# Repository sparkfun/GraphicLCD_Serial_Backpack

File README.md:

Graphic LCD Serial Backpack
============================
[
*Graphic LCD Serial Backpack(LCD-09352)*](https://www.sparkfun.com/products/9352)

The Graphic LCD Serial Backpack interfaces to either the [160x128 pixel Huge Graphic LCD](https://www.sparkfun.com/products/8799) or
the [128x64 pixel display](https://www.sparkfun.com/products/710). The backpack will allow you to write text, draw lines, circles and boxes, 
set and reset individual pixels, and erase specific blocks of the display. 

Repository Contents
-------------------
* **/Firmware** - The firmware that comes installed on the backpack
* **/Hardware** - All Eagle design files (.brd, .sch)

Product Versions
----------------
* [LCD-09352](https://www.sparkfun.com/products/9352)- Graphic Serial LCD Backpack by itself
* [LCD-09351](https://www.sparkfun.com/products/9351) - Serial Graphic LCD 128x64 (LCD + backpack)
* [LCD-08884](https://www.sparkfun.com/products/8884) - Serial Graphic LCD 160x128 (LCD + backpack)

License Information
-------------------
The hardware is released under [Creative Commons Share-alike 3.0](http://creativecommons.org/licenses/by-sa/3.0/).  
All other code is open source so please feel free to do anything you want with it; you buy me a beer if you use this and we meet someday ([Beerware license](http://en.wikipedia.org/wiki/Beerware)).

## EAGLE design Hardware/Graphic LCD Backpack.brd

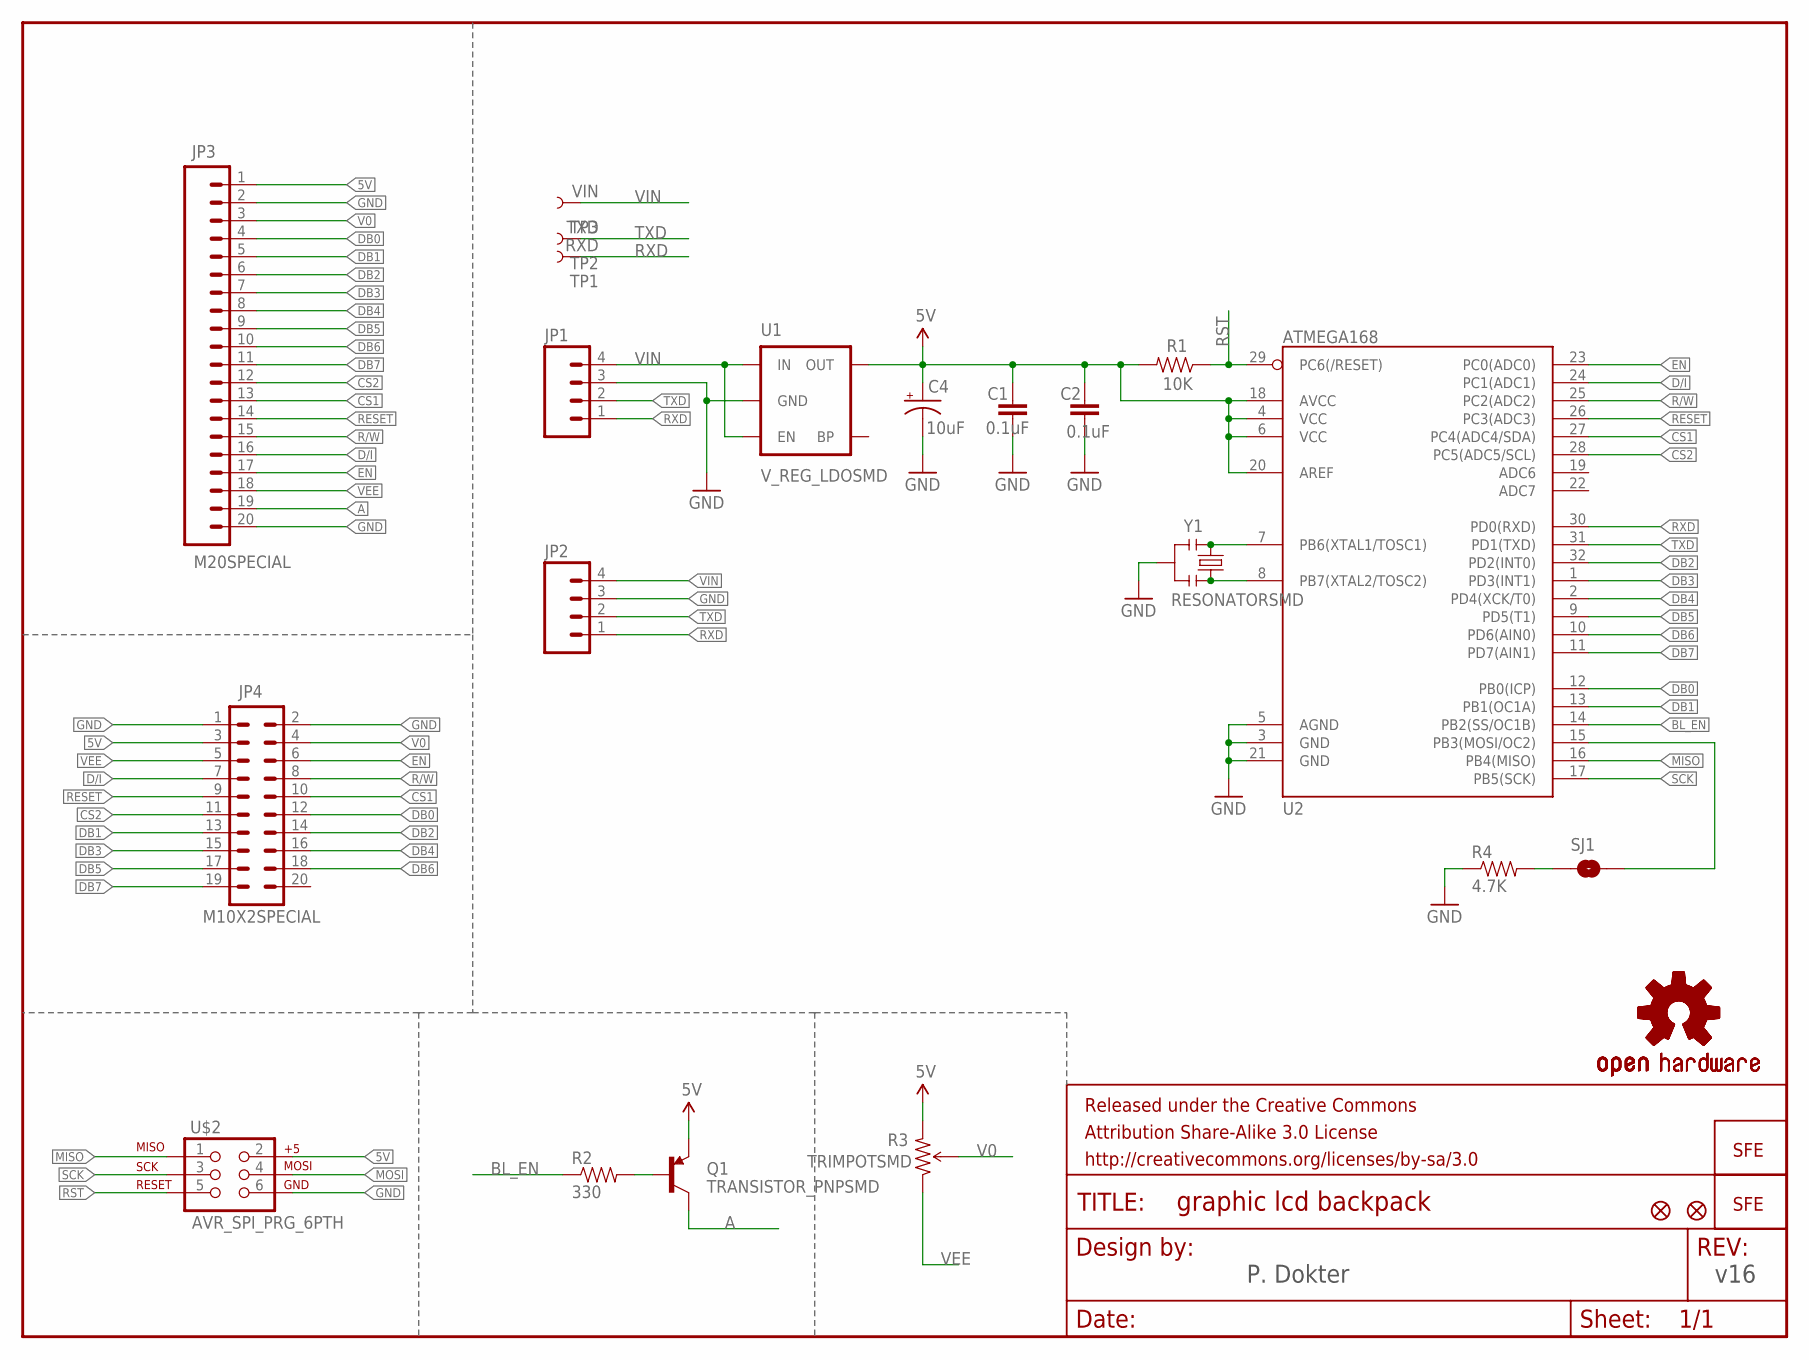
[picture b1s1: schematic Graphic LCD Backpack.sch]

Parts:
C1, C2: 0.1uF; 0603-CAP
C4: 10uF; EIA3216
FRAME1: FRAME-LETTER; CREATIVE_COMMONS
JP1: M04SMD; 1X04-SMD
JP2: M04PTH; 1X04
JP3: M20SPECIAL; 1X20_LOCK_SPECIAL
JP4: M10X2SPECIAL; 2X10_LOCK_SPECIAL
LOGO1: OSHW-LOGOL; OSHW-LOGO-L
LOGO2: LOGO-SFENEW; SFE-NEW-WEBLOGO
LOGO3: OSHW-LOGOS; OSHW-LOGO-S
Q1: TRANSISTOR_PNPSMD; SOT23-3
R1: 10K; 0603-RES
R2: 330; 0603-RES
R3: TRIMPOTSMD; TRIMPOT-3MM
R4: 4.7K; 0603-RES
SJ1: SOLDERJUMPERNC2; SJ_2S-NOTRACE
TP1: RXD; PAD.03X.05
TP2: TXD; PAD.03X.05
TP3: VIN; PAD.03X.05
U1: V_REG_LDOSMD; SOT23-5
U2: ATMEGA168; TQFP32-08
U$2: AVR_SPI_PRG_6PTH; 2X3
U$8: LOGO-SFENEW; SFE-NEW-WEBLOGO
U$9, U$10: FIDUCIAL1X2; FIDUCIAL-1X2
Y1: RESONATORSMD; RESONATOR-SMD

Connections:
5V: C1.1, C2.2, C4.A (+), JP3.1, JP4.3, Q1.2 (E), R1.2, R3.3 (CW), U1.5 (OUT), U2.4 (VCC), U2.6 (VCC), U2.18 (AVCC), U2.20 (AREF), U$2.2
A: JP3.19, Q1.3 (C)
BL_EN: R2.1, U2.14 (PB2(SS/OC1B))
CS1: JP3.13, JP4.10, U2.27 (PC4(ADC4/SDA))
CS2: JP3.12, JP4.11, U2.28 (PC5(ADC5/SCL))
D/I: JP3.16, JP4.7, U2.24 (PC1(ADC1))
DB0: JP3.4, JP4.12, U2.12 (PB0(ICP))
DB1: JP3.5, JP4.13, U2.13 (PB1(OC1A))
DB2: JP3.6, JP4.14, U2.32 (PD2(INT0))
DB3: JP3.7, JP4.15, U2.1 (PD3(INT1))
DB4: JP3.8, JP4.16, U2.2 (PD4(XCK/T0))
DB5: JP3.9, JP4.17, U2.9 (PD5(T1))
DB6: JP3.10, JP4.18, U2.10 (PD6(AIN0))
DB7: JP3.11, JP4.19, U2.11 (PD7(AIN1))
EN: JP3.17, JP4.6, U2.23 (PC0(ADC0))
GND: C1.2, C2.1, C4.C (-), JP1.3, JP2.3, JP3.2, JP3.20, JP4.1, JP4.2, R4.1, U1.2 (GND), U2.3 (GND), U2.5 (AGND), U2.21 (GND), U$2.6, Y1.2
MISO: U2.16 (PB4(MISO)), U$2.1
MOSI: SJ1.2, U2.15 (PB3(MOSI/OC2)), U$2.4
unnamed: Q1.1 (B), R2.2
unnamed: U2.7 (PB6(XTAL1/TOSC1)), Y1.1
unnamed: U2.8 (PB7(XTAL2/TOSC2)), Y1.3
unnamed: R4.2, SJ1.1
R/W: JP3.15, JP4.8, U2.25 (PC2(ADC2))
RESET: JP3.14, JP4.9, U2.26 (PC3(ADC3))
RST: R1.1, U2.29 (PC6(/RESET)), U$2.5
RXD: JP1.1, JP2.1, TP1.P$1, U2.30 (PD0(RXD))
SCK: U2.17 (PB5(SCK)), U$2.3
TXD: JP1.2, JP2.2, TP2.P$1, U2.31 (PD1(TXD))
V0: JP3.3, JP4.4, R3.2 (WIPER)
VEE: JP3.18, JP4.5, R3.1 (CCW)
VIN: JP1.4, JP2.4, TP3.P$1, U1.1 (IN), U1.3 (EN)

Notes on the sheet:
v16
P. Dokter

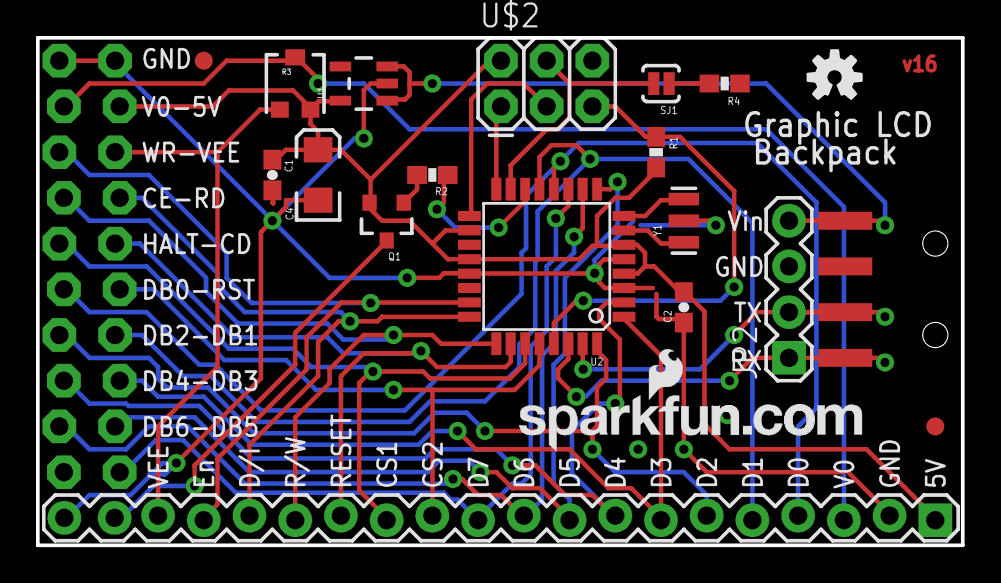
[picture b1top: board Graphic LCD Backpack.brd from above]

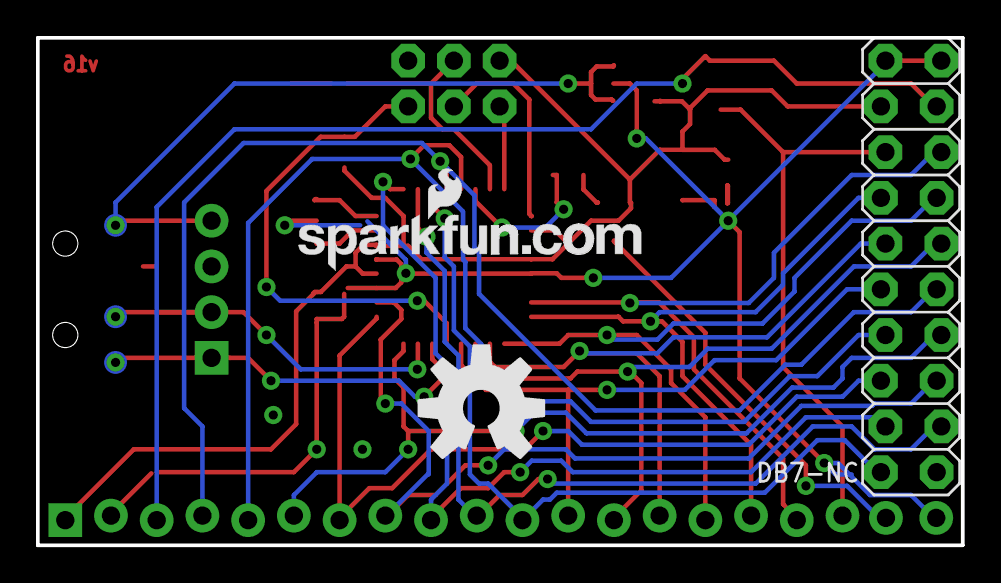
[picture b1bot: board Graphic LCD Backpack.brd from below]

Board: 2 copper layers, 51.4 x 28.2 mm, 27 parts (6 on the bottom side), 31 nets.

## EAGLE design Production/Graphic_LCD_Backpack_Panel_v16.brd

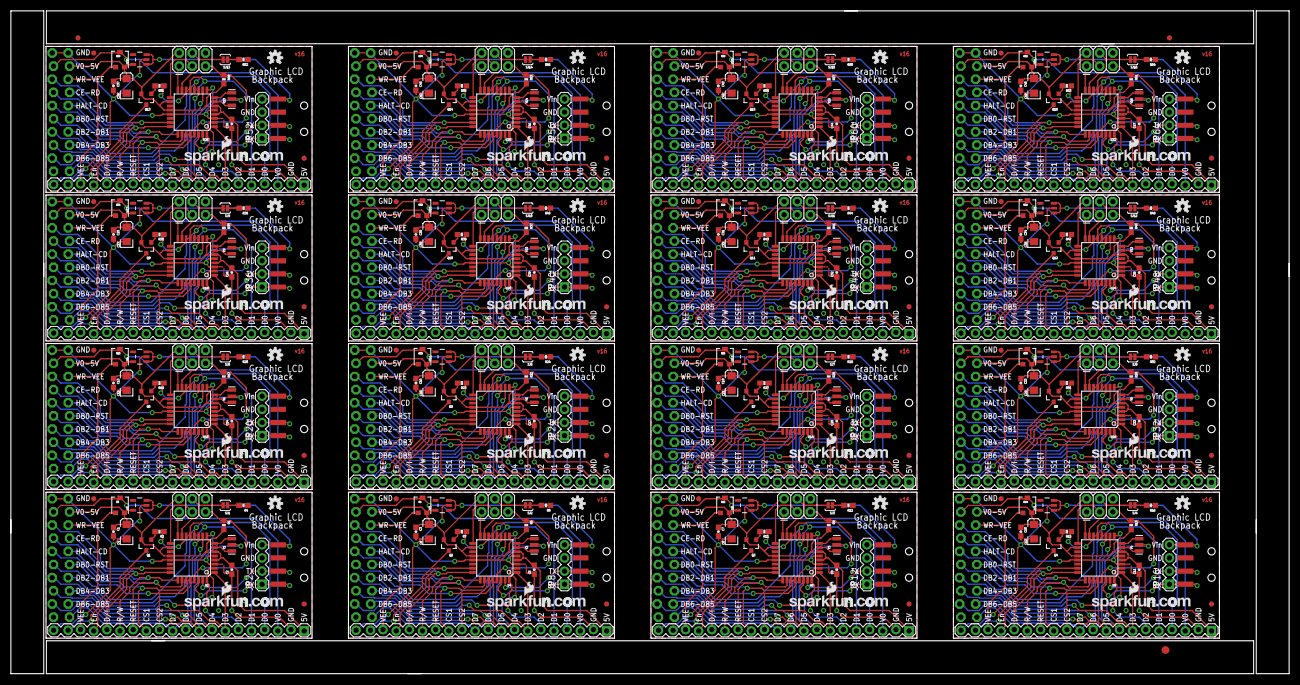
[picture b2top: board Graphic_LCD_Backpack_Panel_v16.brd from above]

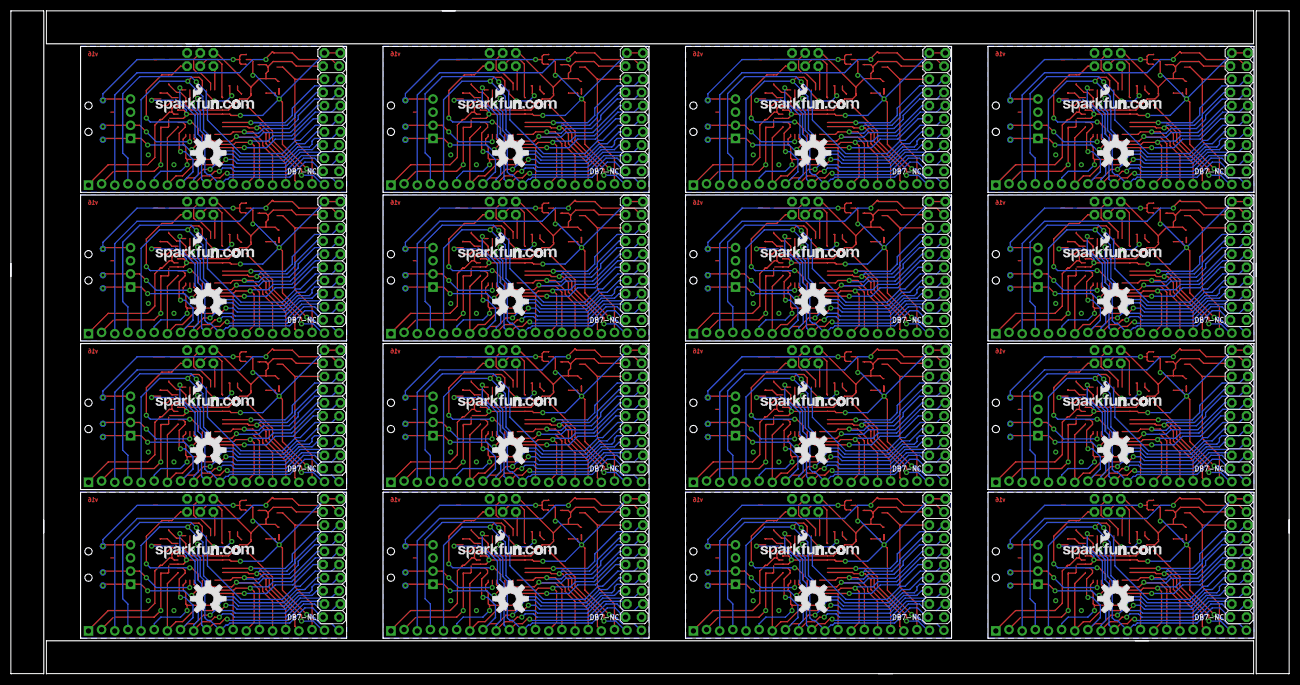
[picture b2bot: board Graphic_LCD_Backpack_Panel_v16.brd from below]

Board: 2 copper layers, 246.9 x 128.0 mm, 419 parts (96 on the bottom side), 496 nets.

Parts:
C1, C2, C3, C5, C7, C8, C10, C11, C13, C14, C16, C17, C19, C20, C22, C23, C25, C26, C28, C29, C31, C32, C34, C35, C37, C38, C40, C41, C43, C44, C46, C47: 0.1uF; 0603-CAP
C4, C6, C9, C12, C15, C18, C21, C24, C27, C30, C33, C36, C39, C42, C45, C48: 10uF; EIA3216
E$1: FIDUCIAL-1.5X3
E$7, E$8: FIDUCIAL-1X2
JP1, JP7, JP11, JP15, JP19, JP23, JP27, JP31, JP35, JP39, JP43, JP47, JP51, JP55, JP59, JP63: 1X04-SMD
JP2, JP8, JP12, JP16, JP20, JP24, JP28, JP32, JP36, JP40, JP44, JP48, JP52, JP56, JP60, JP64: 1X04
JP3, JP5, JP9, JP13, JP17, JP21, JP25, JP29, JP33, JP37, JP41, JP45, JP49, JP53, JP57, JP61: M20SPECIAL; 1X20_LOCK_SPECIAL
JP4, JP6, JP10, JP14, JP18, JP22, JP26, JP30, JP34, JP38, JP42, JP46, JP50, JP54, JP58, JP62: M10X2SPECIAL; 2X10_LOCK_SPECIAL
LOGO1, LOGO4, LOGO7, LOGO10, LOGO13, LOGO16, LOGO19, LOGO22, LOGO25, LOGO28, LOGO31, LOGO34, LOGO37, LOGO40, LOGO43, LOGO46: OSHW-LOGOL; OSHW-LOGO-L
LOGO2, LOGO5, LOGO8, LOGO11, LOGO14, LOGO17, LOGO20, LOGO23, LOGO26, LOGO29, LOGO32, LOGO35, LOGO38, LOGO41, LOGO44, LOGO47: LOGO-SFENEW; SFE-NEW-WEBLOGO
LOGO3, LOGO6, LOGO9, LOGO12, LOGO15, LOGO18, LOGO21, LOGO24, LOGO27, LOGO30, LOGO33, LOGO36, LOGO39, LOGO42, LOGO45, LOGO48: OSHW-LOGOS; OSHW-LOGO-S
Q1, Q2, Q3, Q4, Q5, Q6, Q7, Q8, Q9, Q10, Q11, Q12, Q13, Q14, Q15, Q16: TRANSISTOR_PNPSMD; SOT23-3
R1, R5, R9, R13, R17, R21, R25, R29, R33, R37, R41, R45, R49, R53, R57, R61: 10K; 0603-RES
R2, R7, R11, R15, R19, R23, R27, R31, R35, R39, R43, R47, R51, R55, R59, R63: 330; 0603-RES
R3, R6, R10, R14, R18, R22, R26, R30, R34, R38, R42, R46, R50, R54, R58, R62: TRIMPOTSMD; TRIMPOT-3MM
R4, R8, R12, R16, R20, R24, R28, R32, R36, R40, R44, R48, R52, R56, R60, R64: 4.7K; 0603-RES
SJ1, SJ2, SJ3, SJ4, SJ5, SJ6, SJ7, SJ8, SJ9, SJ10, SJ11, SJ12, SJ13, SJ14, SJ15, SJ16: SOLDERJUMPERNC2; SJ_2S-NOTRACE
TP1, TP4, TP7, TP10, TP13, TP16, TP19, TP22, TP25, TP28, TP31, TP34, TP37, TP40, TP43, TP46: RXD; PAD.03X.05
TP2, TP5, TP8, TP11, TP14, TP17, TP20, TP23, TP26, TP29, TP32, TP35, TP38, TP41, TP44, TP47: TXD; PAD.03X.05
TP3, TP6, TP9, TP12, TP15, TP18, TP21, TP24, TP27, TP30, TP33, TP36, TP39, TP42, TP45, TP48: VIN; PAD.03X.05
U1, U3, U5, U7, U9, U11, U13, U15, U17, U19, U21, U23, U25, U27, U29, U31: V_REG_LDOSMD; SOT23-5
U2, U4, U6, U8, U10, U12, U14, U16, U18, U20, U22, U24, U26, U28, U30, U32: ATMEGA168; TQFP32-08
U$1, U$6, U$8, U$13, U$17, U$21, U$25, U$29, U$33, U$37, U$41, U$45, U$49, U$53, U$57, U$61: LOGO-SFENEW; SFE-NEW-WEBLOGO
U$2, U$5, U$12, U$16, U$20, U$24, U$28, U$32, U$36, U$40, U$44, U$48, U$52, U$56, U$60, U$64: AVR_SPI_PRG_6PTH; 2X3
U$3, U$4, U$7, U$9, U$10, U$11, U$14, U$15, U$18, U$19, U$22, U$23, U$26, U$27, U$30, U$31, U$34, U$35, U$38, U$39, U$42, U$43, U$46, U$47, U$50, U$51, U$54, U$55, U$58, U$59, U$62, U$63: FIDUCIAL1X2; FIDUCIAL-1X2
Y1, Y2, Y3, Y4, Y5, Y6, Y7, Y8, Y9, Y10, Y11, Y12, Y13, Y14, Y15, Y16: RESONATORSMD; RESONATOR-SMD

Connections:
5V: C1.1, C2.2, C4.A, JP3.1, JP4.3, Q1.2, R1.2, R3.3, U1.5, U2.4, U2.6, U2.18, U2.20, U$2.2
5V1: C3.1, C5.2, C6.A, JP5.1, JP6.3, Q2.2, R5.2, R6.3, U3.5, U4.4, U4.6, U4.18, U4.20, U$5.2
5V2: C7.1, C8.2, C9.A, JP9.1, JP10.3, Q3.2, R9.2, R10.3, U5.5, U6.4, U6.6, U6.18, U6.20, U$12.2
5V3: C10.1, C11.2, C12.A, JP13.1, JP14.3, Q4.2, R13.2, R14.3, U7.5, U8.4, U8.6, U8.18, U8.20, U$16.2
5V4: C13.1, C14.2, C15.A, JP17.1, JP18.3, Q5.2, R17.2, R18.3, U9.5, U10.4, U10.6, U10.18, U10.20, U$20.2
5V5: C16.1, C17.2, C18.A, JP21.1, JP22.3, Q6.2, R21.2, R22.3, U11.5, U12.4, U12.6, U12.18, U12.20, U$24.2
5V6: C19.1, C20.2, C21.A, JP25.1, JP26.3, Q7.2, R25.2, R26.3, U13.5, U14.4, U14.6, U14.18, U14.20, U$28.2
5V7: C22.1, C23.2, C24.A, JP29.1, JP30.3, Q8.2, R29.2, R30.3, U15.5, U16.4, U16.6, U16.18, U16.20, U$32.2
5V8: C25.1, C26.2, C27.A, JP33.1, JP34.3, Q9.2, R33.2, R34.3, U17.5, U18.4, U18.6, U18.18, U18.20, U$36.2
5V9: C28.1, C29.2, C30.A, JP37.1, JP38.3, Q10.2, R37.2, R38.3, U19.5, U20.4, U20.6, U20.18, U20.20, U$40.2
5V10: C31.1, C32.2, C33.A, JP41.1, JP42.3, Q11.2, R41.2, R42.3, U21.5, U22.4, U22.6, U22.18, U22.20, U$44.2
5V11: C34.1, C35.2, C36.A, JP45.1, JP46.3, Q12.2, R45.2, R46.3, U23.5, U24.4, U24.6, U24.18, U24.20, U$48.2
5V12: C37.1, C38.2, C39.A, JP49.1, JP50.3, Q13.2, R49.2, R50.3, U25.5, U26.4, U26.6, U26.18, U26.20, U$52.2
5V13: C40.1, C41.2, C42.A, JP53.1, JP54.3, Q14.2, R53.2, R54.3, U27.5, U28.4, U28.6, U28.18, U28.20, U$56.2
5V14: C43.1, C44.2, C45.A, JP57.1, JP58.3, Q15.2, R57.2, R58.3, U29.5, U30.4, U30.6, U30.18, U30.20, U$60.2
5V15: C46.1, C47.2, C48.A, JP61.1, JP62.3, Q16.2, R61.2, R62.3, U31.5, U32.4, U32.6, U32.18, U32.20, U$64.2
A: JP3.19, Q1.3
A1: JP5.19, Q2.3
A2: JP9.19, Q3.3
A3: JP13.19, Q4.3
A4: JP17.19, Q5.3
A5: JP21.19, Q6.3
A6: JP25.19, Q7.3
A7: JP29.19, Q8.3
A8: JP33.19, Q9.3
A9: JP37.19, Q10.3
A10: JP41.19, Q11.3
A11: JP45.19, Q12.3
A12: JP49.19, Q13.3
A13: JP53.19, Q14.3
A14: JP57.19, Q15.3
A15: JP61.19, Q16.3
BL_EN: R2.1, U2.14
BL_EN1: R7.1, U4.14
BL_EN2: R11.1, U6.14
BL_EN3: R15.1, U8.14
BL_EN4: R19.1, U10.14
BL_EN5: R23.1, U12.14
BL_EN6: R27.1, U14.14
BL_EN7: R31.1, U16.14
BL_EN8: R35.1, U18.14
BL_EN9: R39.1, U20.14
BL_EN10: R43.1, U22.14
BL_EN11: R47.1, U24.14
BL_EN12: R51.1, U26.14
BL_EN13: R55.1, U28.14
BL_EN14: R59.1, U30.14
BL_EN15: R63.1, U32.14
CS1: JP3.13, JP4.10, U2.27
CS2: JP3.12, JP4.11, U2.28
CS3: JP5.12, JP6.11, U4.28
CS4: JP5.13, JP6.10, U4.27
CS5: JP9.12, JP10.11, U6.28
CS6: JP9.13, JP10.10, U6.27
CS7: JP13.12, JP14.11, U8.28
CS8: JP13.13, JP14.10, U8.27
CS9: JP17.12, JP18.11, U10.28
CS10: JP17.13, JP18.10, U10.27
CS11: JP21.12, JP22.11, U12.28
CS12: JP21.13, JP22.10, U12.27
CS13: JP25.12, JP26.11, U14.28
CS14: JP25.13, JP26.10, U14.27
CS15: JP29.12, JP30.11, U16.28
CS16: JP29.13, JP30.10, U16.27
CS17: JP33.12, JP34.11, U18.28
CS18: JP33.13, JP34.10, U18.27
CS19: JP37.12, JP38.11, U20.28
CS20: JP37.13, JP38.10, U20.27
CS21: JP41.12, JP42.11, U22.28
CS22: JP41.13, JP42.10, U22.27
CS23: JP45.12, JP46.11, U24.28
CS24: JP45.13, JP46.10, U24.27
CS25: JP49.12, JP50.11, U26.28
CS26: JP49.13, JP50.10, U26.27
CS27: JP53.12, JP54.11, U28.28
CS28: JP53.13, JP54.10, U28.27
CS29: JP57.12, JP58.11, U30.28
CS30: JP57.13, JP58.10, U30.27
CS31: JP61.12, JP62.11, U32.28
CS32: JP61.13, JP62.10, U32.27
D/I: JP3.16, JP4.7, U2.24
D/I1: JP5.16, JP6.7, U4.24
D/I2: JP9.16, JP10.7, U6.24
D/I3: JP13.16, JP14.7, U8.24
D/I4: JP17.16, JP18.7, U10.24
D/I5: JP21.16, JP22.7, U12.24
D/I6: JP25.16, JP26.7, U14.24
D/I7: JP29.16, JP30.7, U16.24
D/I8: JP33.16, JP34.7, U18.24
D/I9: JP37.16, JP38.7, U20.24
D/I10: JP41.16, JP42.7, U22.24
D/I11: JP45.16, JP46.7, U24.24
D/I12: JP49.16, JP50.7, U26.24
D/I13: JP53.16, JP54.7, U28.24
D/I14: JP57.16, JP58.7, U30.24
D/I15: JP61.16, JP62.7, U32.24
DB0: JP3.4, JP4.12, U2.12
DB1: JP3.5, JP4.13, U2.13
DB2: JP3.6, JP4.14, U2.32
DB3: JP3.7, JP4.15, U2.1
DB4: JP3.8, JP4.16, U2.2
DB5: JP3.9, JP4.17, U2.9
DB6: JP3.10, JP4.18, U2.10
DB7: JP3.11, JP4.19, U2.11
DB8: JP5.4, JP6.12, U4.12
DB9: JP5.5, JP6.13, U4.13
DB10: JP5.6, JP6.14, U4.32
DB11: JP5.7, JP6.15, U4.1
DB12: JP5.8, JP6.16, U4.2
DB13: JP5.9, JP6.17, U4.9
DB14: JP5.10, JP6.18, U4.10
DB15: JP5.11, JP6.19, U4.11
DB16: JP9.4, JP10.12, U6.12
DB17: JP9.5, JP10.13, U6.13
DB18: JP9.6, JP10.14, U6.32
DB19: JP9.7, JP10.15, U6.1
DB20: JP9.8, JP10.16, U6.2
DB21: JP9.9, JP10.17, U6.9
DB22: JP9.10, JP10.18, U6.10
DB23: JP9.11, JP10.19, U6.11
DB24: JP13.4, JP14.12, U8.12
DB25: JP13.5, JP14.13, U8.13
DB26: JP13.6, JP14.14, U8.32
DB27: JP13.7, JP14.15, U8.1
DB28: JP13.8, JP14.16, U8.2
DB29: JP13.9, JP14.17, U8.9
DB30: JP13.10, JP14.18, U8.10
DB31: JP13.11, JP14.19, U8.11
DB32: JP17.4, JP18.12, U10.12
DB33: JP17.5, JP18.13, U10.13
DB34: JP17.6, JP18.14, U10.32
DB35: JP17.7, JP18.15, U10.1
DB36: JP17.8, JP18.16, U10.2
DB37: JP17.9, JP18.17, U10.9
DB38: JP17.10, JP18.18, U10.10
DB39: JP17.11, JP18.19, U10.11
DB40: JP21.4, JP22.12, U12.12
DB41: JP21.5, JP22.13, U12.13
DB42: JP21.6, JP22.14, U12.32
DB43: JP21.7, JP22.15, U12.1
DB44: JP21.8, JP22.16, U12.2
DB45: JP21.9, JP22.17, U12.9
DB46: JP21.10, JP22.18, U12.10
DB47: JP21.11, JP22.19, U12.11
DB48: JP25.4, JP26.12, U14.12
DB49: JP25.5, JP26.13, U14.13
DB50: JP25.6, JP26.14, U14.32
DB51: JP25.7, JP26.15, U14.1
DB52: JP25.8, JP26.16, U14.2
DB53: JP25.9, JP26.17, U14.9
DB54: JP25.10, JP26.18, U14.10
DB55: JP25.11, JP26.19, U14.11
DB56: JP29.4, JP30.12, U16.12
DB57: JP29.5, JP30.13, U16.13
DB58: JP29.6, JP30.14, U16.32
DB59: JP29.7, JP30.15, U16.1
DB60: JP29.8, JP30.16, U16.2
DB61: JP29.9, JP30.17, U16.9
DB62: JP29.10, JP30.18, U16.10
DB63: JP29.11, JP30.19, U16.11
DB64: JP33.4, JP34.12, U18.12
DB65: JP33.5, JP34.13, U18.13
DB66: JP33.6, JP34.14, U18.32
DB67: JP33.7, JP34.15, U18.1
DB68: JP33.8, JP34.16, U18.2
DB69: JP33.9, JP34.17, U18.9
DB70: JP33.10, JP34.18, U18.10
DB71: JP33.11, JP34.19, U18.11
DB72: JP37.4, JP38.12, U20.12
DB73: JP37.5, JP38.13, U20.13
DB74: JP37.6, JP38.14, U20.32
DB75: JP37.7, JP38.15, U20.1
DB76: JP37.8, JP38.16, U20.2
DB77: JP37.9, JP38.17, U20.9
DB78: JP37.10, JP38.18, U20.10
DB79: JP37.11, JP38.19, U20.11
DB80: JP41.4, JP42.12, U22.12
DB81: JP41.5, JP42.13, U22.13
DB82: JP41.6, JP42.14, U22.32
DB83: JP41.7, JP42.15, U22.1
DB84: JP41.8, JP42.16, U22.2
DB85: JP41.9, JP42.17, U22.9
DB86: JP41.10, JP42.18, U22.10
DB87: JP41.11, JP42.19, U22.11
DB88: JP45.4, JP46.12, U24.12
DB89: JP45.5, JP46.13, U24.13
DB90: JP45.6, JP46.14, U24.32
DB91: JP45.7, JP46.15, U24.1
DB92: JP45.8, JP46.16, U24.2
DB93: JP45.9, JP46.17, U24.9
DB94: JP45.10, JP46.18, U24.10
DB95: JP45.11, JP46.19, U24.11
DB96: JP49.4, JP50.12, U26.12
DB97: JP49.5, JP50.13, U26.13
DB98: JP49.6, JP50.14, U26.32
DB99: JP49.7, JP50.15, U26.1
DB100: JP49.8, JP50.16, U26.2
DB101: JP49.9, JP50.17, U26.9
DB102: JP49.10, JP50.18, U26.10
DB103: JP49.11, JP50.19, U26.11
DB104: JP53.4, JP54.12, U28.12
DB105: JP53.5, JP54.13, U28.13
DB106: JP53.6, JP54.14, U28.32
DB107: JP53.7, JP54.15, U28.1
DB108: JP53.8, JP54.16, U28.2
DB109: JP53.9, JP54.17, U28.9
DB110: JP53.10, JP54.18, U28.10
DB111: JP53.11, JP54.19, U28.11
DB112: JP57.4, JP58.12, U30.12
DB113: JP57.5, JP58.13, U30.13
DB114: JP57.6, JP58.14, U30.32
DB115: JP57.7, JP58.15, U30.1
DB116: JP57.8, JP58.16, U30.2
DB117: JP57.9, JP58.17, U30.9
DB118: JP57.10, JP58.18, U30.10
DB119: JP57.11, JP58.19, U30.11
DB120: JP61.4, JP62.12, U32.12
DB121: JP61.5, JP62.13, U32.13
DB122: JP61.6, JP62.14, U32.32
DB123: JP61.7, JP62.15, U32.1
DB124: JP61.8, JP62.16, U32.2
DB125: JP61.9, JP62.17, U32.9
DB126: JP61.10, JP62.18, U32.10
DB127: JP61.11, JP62.19, U32.11
EN: JP3.17, JP4.6, U2.23
EN1: JP5.17, JP6.6, U4.23
EN2: JP9.17, JP10.6, U6.23
EN3: JP13.17, JP14.6, U8.23
EN4: JP17.17, JP18.6, U10.23
EN5: JP21.17, JP22.6, U12.23
EN6: JP25.17, JP26.6, U14.23
EN7: JP29.17, JP30.6, U16.23
EN8: JP33.17, JP34.6, U18.23
EN9: JP37.17, JP38.6, U20.23
EN10: JP41.17, JP42.6, U22.23
EN11: JP45.17, JP46.6, U24.23
EN12: JP49.17, JP50.6, U26.23
EN13: JP53.17, JP54.6, U28.23
EN14: JP57.17, JP58.6, U30.23
EN15: JP61.17, JP62.6, U32.23
GND: C1.2, C2.1, C4.C, JP1.3, JP2.3, JP3.2, JP3.20, JP4.1, JP4.2, R4.1, U1.2, U2.3, U2.5, U2.21, U$2.6, Y1.2
GND1: C3.2, C5.1, C6.C, JP5.2, JP5.20, JP6.1, JP6.2, JP7.3, JP8.3, R8.1, U3.2, U4.3, U4.5, U4.21, U$5.6, Y2.2
GND2: C7.2, C8.1, C9.C, JP9.2, JP9.20, JP10.1, JP10.2, JP11.3, JP12.3, R12.1, U5.2, U6.3, U6.5, U6.21, U$12.6, Y3.2
GND3: C10.2, C11.1, C12.C, JP13.2, JP13.20, JP14.1, JP14.2, JP15.3, JP16.3, R16.1, U7.2, U8.3, U8.5, U8.21, U$16.6, Y4.2
GND4: C13.2, C14.1, C15.C, JP17.2, JP17.20, JP18.1, JP18.2, JP19.3, JP20.3, R20.1, U9.2, U10.3, U10.5, U10.21, U$20.6, Y5.2
GND5: C16.2, C17.1, C18.C, JP21.2, JP21.20, JP22.1, JP22.2, JP23.3, JP24.3, R24.1, U11.2, U12.3, U12.5, U12.21, U$24.6, Y6.2
GND6: C19.2, C20.1, C21.C, JP25.2, JP25.20, JP26.1, JP26.2, JP27.3, JP28.3, R28.1, U13.2, U14.3, U14.5, U14.21, U$28.6, Y7.2
GND7: C22.2, C23.1, C24.C, JP29.2, JP29.20, JP30.1, JP30.2, JP31.3, JP32.3, R32.1, U15.2, U16.3, U16.5, U16.21, U$32.6, Y8.2
GND8: C25.2, C26.1, C27.C, JP33.2, JP33.20, JP34.1, JP34.2, JP35.3, JP36.3, R36.1, U17.2, U18.3, U18.5, U18.21, U$36.6, Y9.2
GND9: C28.2, C29.1, C30.C, JP37.2, JP37.20, JP38.1, JP38.2, JP39.3, JP40.3, R40.1, U19.2, U20.3, U20.5, U20.21, U$40.6, Y10.2
GND10: C31.2, C32.1, C33.C, JP41.2, JP41.20, JP42.1, JP42.2, JP43.3, JP44.3, R44.1, U21.2, U22.3, U22.5, U22.21, U$44.6, Y11.2
GND11: C34.2, C35.1, C36.C, JP45.2, JP45.20, JP46.1, JP46.2, JP47.3, JP48.3, R48.1, U23.2, U24.3, U24.5, U24.21, U$48.6, Y12.2
GND12: C37.2, C38.1, C39.C, JP49.2, JP49.20, JP50.1, JP50.2, JP51.3, JP52.3, R52.1, U25.2, U26.3, U26.5, U26.21, U$52.6, Y13.2
GND13: C40.2, C41.1, C42.C, JP53.2, JP53.20, JP54.1, JP54.2, JP55.3, JP56.3, R56.1, U27.2, U28.3, U28.5, U28.21, U$56.6, Y14.2
GND14: C43.2, C44.1, C45.C, JP57.2, JP57.20, JP58.1, JP58.2, JP59.3, JP60.3, R60.1, U29.2, U30.3, U30.5, U30.21, U$60.6, Y15.2
GND15: C46.2, C47.1, C48.C, JP61.2, JP61.20, JP62.1, JP62.2, JP63.3, JP64.3, R64.1, U31.2, U32.3, U32.5, U32.21, U$64.6, Y16.2
MISO: U2.16, U$2.1
MISO1: U4.16, U$5.1
MISO2: U6.16, U$12.1
MISO3: U8.16, U$16.1
MISO4: U10.16, U$20.1
MISO5: U12.16, U$24.1
MISO6: U14.16, U$28.1
MISO7: U16.16, U$32.1
MISO8: U18.16, U$36.1
MISO9: U20.16, U$40.1
MISO10: U22.16, U$44.1
MISO11: U24.16, U$48.1
MISO12: U26.16, U$52.1
MISO13: U28.16, U$56.1
MISO14: U30.16, U$60.1
MISO15: U32.16, U$64.1
MOSI: SJ1.2, U2.15, U$2.4
MOSI1: SJ2.2, U4.15, U$5.4
MOSI2: SJ3.2, U6.15, U$12.4
MOSI3: SJ4.2, U8.15, U$16.4
MOSI4: SJ5.2, U10.15, U$20.4
MOSI5: SJ6.2, U12.15, U$24.4
MOSI6: SJ7.2, U14.15, U$28.4
MOSI7: SJ8.2, U16.15, U$32.4
MOSI8: SJ9.2, U18.15, U$36.4
MOSI9: SJ10.2, U20.15, U$40.4
MOSI10: SJ11.2, U22.15, U$44.4
MOSI11: SJ12.2, U24.15, U$48.4
MOSI12: SJ13.2, U26.15, U$52.4
MOSI13: SJ14.2, U28.15, U$56.4
MOSI14: SJ15.2, U30.15, U$60.4
MOSI15: SJ16.2, U32.15, U$64.4
unnamed: Q1.1, R2.2
unnamed: U2.7, Y1.1
unnamed: U2.8, Y1.3
unnamed: R4.2, SJ1.1
unnamed: Q2.1, R7.2
unnamed: U4.7, Y2.1
unnamed: U4.8, Y2.3
unnamed: R8.2, SJ2.1
unnamed: Q3.1, R11.2
unnamed: U6.7, Y3.1
unnamed: U6.8, Y3.3
unnamed: R12.2, SJ3.1
unnamed: Q4.1, R15.2
unnamed: U8.7, Y4.1
unnamed: U8.8, Y4.3
unnamed: R16.2, SJ4.1
unnamed: Q5.1, R19.2
unnamed: U10.7, Y5.1
unnamed: U10.8, Y5.3
unnamed: R20.2, SJ5.1
unnamed: Q6.1, R23.2
unnamed: U12.7, Y6.1
unnamed: U12.8, Y6.3
unnamed: R24.2, SJ6.1
unnamed: Q7.1, R27.2
unnamed: U14.7, Y7.1
unnamed: U14.8, Y7.3
unnamed: R28.2, SJ7.1
unnamed: Q8.1, R31.2
unnamed: U16.7, Y8.1
unnamed: U16.8, Y8.3
unnamed: R32.2, SJ8.1
unnamed: Q9.1, R35.2
unnamed: U18.7, Y9.1
unnamed: U18.8, Y9.3
unnamed: R36.2, SJ9.1
unnamed: Q10.1, R39.2
unnamed: U20.7, Y10.1
unnamed: U20.8, Y10.3
unnamed: R40.2, SJ10.1
unnamed: Q11.1, R43.2
unnamed: U22.7, Y11.1
unnamed: U22.8, Y11.3
unnamed: R44.2, SJ11.1
unnamed: Q12.1, R47.2
unnamed: U24.7, Y12.1
unnamed: U24.8, Y12.3
unnamed: R48.2, SJ12.1
unnamed: Q13.1, R51.2
unnamed: U26.7, Y13.1
unnamed: U26.8, Y13.3
unnamed: R52.2, SJ13.1
unnamed: Q14.1, R55.2
unnamed: U28.7, Y14.1
unnamed: U28.8, Y14.3
unnamed: R56.2, SJ14.1
unnamed: Q15.1, R59.2
unnamed: U30.7, Y15.1
unnamed: U30.8, Y15.3
unnamed: R60.2, SJ15.1
unnamed: Q16.1, R63.2
unnamed: U32.7, Y16.1
unnamed: U32.8, Y16.3
unnamed: R64.2, SJ16.1
R/W: JP3.15, JP4.8, U2.25
R/W1: JP5.15, JP6.8, U4.25
R/W2: JP9.15, JP10.8, U6.25
R/W3: JP13.15, JP14.8, U8.25
R/W4: JP17.15, JP18.8, U10.25
R/W5: JP21.15, JP22.8, U12.25
R/W6: JP25.15, JP26.8, U14.25
R/W7: JP29.15, JP30.8, U16.25
R/W8: JP33.15, JP34.8, U18.25
R/W9: JP37.15, JP38.8, U20.25
R/W10: JP41.15, JP42.8, U22.25
R/W11: JP45.15, JP46.8, U24.25
R/W12: JP49.15, JP50.8, U26.25
R/W13: JP53.15, JP54.8, U28.25
R/W14: JP57.15, JP58.8, U30.25
R/W15: JP61.15, JP62.8, U32.25
RESET: JP3.14, JP4.9, U2.26
RESET1: JP5.14, JP6.9, U4.26
RESET2: JP9.14, JP10.9, U6.26
RESET3: JP13.14, JP14.9, U8.26
RESET4: JP17.14, JP18.9, U10.26
RESET5: JP21.14, JP22.9, U12.26
RESET6: JP25.14, JP26.9, U14.26
RESET7: JP29.14, JP30.9, U16.26
RESET8: JP33.14, JP34.9, U18.26
RESET9: JP37.14, JP38.9, U20.26
RESET10: JP41.14, JP42.9, U22.26
RESET11: JP45.14, JP46.9, U24.26
RESET12: JP49.14, JP50.9, U26.26
RESET13: JP53.14, JP54.9, U28.26
RESET14: JP57.14, JP58.9, U30.26
RESET15: JP61.14, JP62.9, U32.26
RST: R1.1, U2.29, U$2.5
RST1: R5.1, U4.29, U$5.5
RST2: R9.1, U6.29, U$12.5
RST3: R13.1, U8.29, U$16.5
RST4: R17.1, U10.29, U$20.5
RST5: R21.1, U12.29, U$24.5
RST6: R25.1, U14.29, U$28.5
RST7: R29.1, U16.29, U$32.5
RST8: R33.1, U18.29, U$36.5
RST9: R37.1, U20.29, U$40.5
RST10: R41.1, U22.29, U$44.5
RST11: R45.1, U24.29, U$48.5
RST12: R49.1, U26.29, U$52.5
RST13: R53.1, U28.29, U$56.5
RST14: R57.1, U30.29, U$60.5
RST15: R61.1, U32.29, U$64.5
RXD: JP1.1, JP2.1, TP1.P$1, U2.30
RXD1: JP7.1, JP8.1, TP4.P$1, U4.30
RXD2: JP11.1, JP12.1, TP7.P$1, U6.30
RXD3: JP15.1, JP16.1, TP10.P$1, U8.30
RXD4: JP19.1, JP20.1, TP13.P$1, U10.30
RXD5: JP23.1, JP24.1, TP16.P$1, U12.30
RXD6: JP27.1, JP28.1, TP19.P$1, U14.30
RXD7: JP31.1, JP32.1, TP22.P$1, U16.30
RXD8: JP35.1, JP36.1, TP25.P$1, U18.30
RXD9: JP39.1, JP40.1, TP28.P$1, U20.30
RXD10: JP43.1, JP44.1, TP31.P$1, U22.30
RXD11: JP47.1, JP48.1, TP34.P$1, U24.30
RXD12: JP51.1, JP52.1, TP37.P$1, U26.30
RXD13: JP55.1, JP56.1, TP40.P$1, U28.30
RXD14: JP59.1, JP60.1, TP43.P$1, U30.30
RXD15: JP63.1, JP64.1, TP46.P$1, U32.30
SCK: U2.17, U$2.3
SCK1: U4.17, U$5.3
SCK2: U6.17, U$12.3
SCK3: U8.17, U$16.3
SCK4: U10.17, U$20.3
SCK5: U12.17, U$24.3
SCK6: U14.17, U$28.3
SCK7: U16.17, U$32.3
SCK8: U18.17, U$36.3
SCK9: U20.17, U$40.3
SCK10: U22.17, U$44.3
SCK11: U24.17, U$48.3
SCK12: U26.17, U$52.3
SCK13: U28.17, U$56.3
SCK14: U30.17, U$60.3
SCK15: U32.17, U$64.3
TXD: JP1.2, JP2.2, TP2.P$1, U2.31
TXD1: JP7.2, JP8.2, TP5.P$1, U4.31
TXD2: JP11.2, JP12.2, TP8.P$1, U6.31
TXD3: JP15.2, JP16.2, TP11.P$1, U8.31
TXD4: JP19.2, JP20.2, TP14.P$1, U10.31
TXD5: JP23.2, JP24.2, TP17.P$1, U12.31
TXD6: JP27.2, JP28.2, TP20.P$1, U14.31
TXD7: JP31.2, JP32.2, TP23.P$1, U16.31
TXD8: JP35.2, JP36.2, TP26.P$1, U18.31
TXD9: JP39.2, JP40.2, TP29.P$1, U20.31
TXD10: JP43.2, JP44.2, TP32.P$1, U22.31
TXD11: JP47.2, JP48.2, TP35.P$1, U24.31
TXD12: JP51.2, JP52.2, TP38.P$1, U26.31
TXD13: JP55.2, JP56.2, TP41.P$1, U28.31
TXD14: JP59.2, JP60.2, TP44.P$1, U30.31
TXD15: JP63.2, JP64.2, TP47.P$1, U32.31
V0: JP3.3, JP4.4, R3.2
V1: JP5.3, JP6.4, R6.2
V2: JP9.3, JP10.4, R10.2
V3: JP13.3, JP14.4, R14.2
V4: JP17.3, JP18.4, R18.2
V5: JP21.3, JP22.4, R22.2
V6: JP25.3, JP26.4, R26.2
V7: JP29.3, JP30.4, R30.2
V8: JP33.3, JP34.4, R34.2
V9: JP37.3, JP38.4, R38.2
V10: JP41.3, JP42.4, R42.2
V11: JP45.3, JP46.4, R46.2
V12: JP49.3, JP50.4, R50.2
V13: JP53.3, JP54.4, R54.2
V14: JP57.3, JP58.4, R58.2
V15: JP61.3, JP62.4, R62.2
VEE: JP3.18, JP4.5, R3.1
VEE1: JP5.18, JP6.5, R6.1
VEE2: JP9.18, JP10.5, R10.1
VEE3: JP13.18, JP14.5, R14.1
VEE4: JP17.18, JP18.5, R18.1
VEE5: JP21.18, JP22.5, R22.1
VEE6: JP25.18, JP26.5, R26.1
VEE7: JP29.18, JP30.5, R30.1
VEE8: JP33.18, JP34.5, R34.1
VEE9: JP37.18, JP38.5, R38.1
VEE10: JP41.18, JP42.5, R42.1
VEE11: JP45.18, JP46.5, R46.1
VEE12: JP49.18, JP50.5, R50.1
VEE13: JP53.18, JP54.5, R54.1
VEE14: JP57.18, JP58.5, R58.1
VEE15: JP61.18, JP62.5, R62.1
VIN: JP1.4, JP2.4, TP3.P$1, U1.1, U1.3
VIN1: JP7.4, JP8.4, TP6.P$1, U3.1, U3.3
VIN2: JP11.4, JP12.4, TP9.P$1, U5.1, U5.3
VIN3: JP15.4, JP16.4, TP12.P$1, U7.1, U7.3
VIN4: JP19.4, JP20.4, TP15.P$1, U9.1, U9.3
VIN5: JP23.4, JP24.4, TP18.P$1, U11.1, U11.3
VIN6: JP27.4, JP28.4, TP21.P$1, U13.1, U13.3
VIN7: JP31.4, JP32.4, TP24.P$1, U15.1, U15.3
VIN8: JP35.4, JP36.4, TP27.P$1, U17.1, U17.3
VIN9: JP39.4, JP40.4, TP30.P$1, U19.1, U19.3
VIN10: JP43.4, JP44.4, TP33.P$1, U21.1, U21.3
VIN11: JP47.4, JP48.4, TP36.P$1, U23.1, U23.3
VIN12: JP51.4, JP52.4, TP39.P$1, U25.1, U25.3
VIN13: JP55.4, JP56.4, TP42.P$1, U27.1, U27.3
VIN14: JP59.4, JP60.4, TP45.P$1, U29.1, U29.3
VIN15: JP63.4, JP64.4, TP48.P$1, U31.1, U31.3

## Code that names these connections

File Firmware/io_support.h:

/***************************************************************************
io_support.h

Pin definitions and function prototypes for the io_support.c file.

02 May 2013 - Mike Hord, SparkFun Electronics

This code is released under the Creative Commons Attribution Share-Alike 3.0
 license. You are free to reuse, remix, or redistribute it as you see fit,
 so long as you provide attribution to SparkFun Electronics.

***************************************************************************/


#ifndef __io_support_h
#define __io_support_h

// Pinout definitions.

#define nBL_EN 		2	//PB2 is backlight enable, and is active low

// Pins for the ks0108b (128x64) display
#define EN      0	// PC0
#define RS      1	// PC1
#define R_W     2	// PC2
#define RESET   3	// PC3
#define CS1     4	// PC4
#define CS2     5	// PC5

// Pins for the t6963 (160x128) display
#define WR      0	// PC0
#define RD      1	// PC1
#define CE      2	// PC2
#define CD      3	// PC3
#define HALT    4	// PC4
#define RST     5	// PC5

void    ioInit(void);
void    setData(uint8_t data);
uint8_t readData(void);

#endif

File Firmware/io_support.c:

/***************************************************************************
io_support.c

IO support function file for the serial graphical LCD backpack project. This
 file provides an init function for the IO pins, as well as a set/get data
 function which abstracts away the dance you have to do to integrate data
 from two different ports into one byte.

02 May 2013 - Mike Hord, SparkFun Electronics

This code is released under the Creative Commons Attribution Share-Alike 3.0
 license. You are free to reuse, remix, or redistribute it as you see fit,
 so long as you provide attribution to SparkFun Electronics.

***************************************************************************/

#include <avr/io.h>
#include "glcdbp.h"
#include "io_support.h"

// This is setup in glcdbp.c and is used to track the "type" of the display
//  throughout the code.
extern enum DISPLAY_TYPE display;

void ioInit(void)
{
  // Set up the data direction registers for the data bus pins.
  //  The data bus is on PB0:1 and PD2:7, so make those pins outputs.
  DDRB = 0b00001111;
  DDRD = 0b11111100;

  PORTB &= ~(1<<nBL_EN);  // Turn backlight on
  
  // Now we need to configure the I/O to support the two types of display.
  if (display == SMALL)
  {
    DDRC =  ((1<<EN) | (1<<RS) | (1<<R_W) | (1<<RESET) | (1<<CS1) | (1<<CS2));
    PORTC = ((1<<EN) | (1<<RS) | (1<<R_W) | (1<<RESET) | (1<<CS1) | (1<<CS2));
  }
  else if (display == LARGE)
  {
    DDRC =  ((1<<WR) | (1<<RD) | (1<<CE) | (1<<CD) | (1<<HALT) | (1<<RST));
    PORTC = ((1<<WR) | (1<<RD) | (1<<CE) | (1<<CD) | (1<<HALT) | (1<<RST));
  }
}

// Abstracts away the fact that the data pins are not on one port. We *could*
//  inline this code whereever necessary, but who wants to read all this?
void setData(uint8_t data)
{
  // Set the port direction registers to make data pins outputs.
  DDRB |= 0x03;
  DDRD |= 0xFC;
  
  PORTB &= 0xFC;    // Clear PB7:2 in preparation for data.
  PORTD &= 0x03;    // Clear PD1:0.
  
  PORTB |= (data & 0x03); // Mask off PB1:0 so we don't change them
                          //  and then write the other 6 bits.
  PORTD |= (data & 0xFC); // Mask off PD7:2 so we don't change them
                          //  and then write the other two bits.
                          //  The data is now in place.
}

// Same deal as setData.
uint8_t readData(void)
{
  // Set the port direction to input.
  DDRB &= ~(0x03);
  DDRD &= ~(0xFC);
  
  // Pull the data in.
  uint8_t data = (PINB & 0x03);
  data |= (PIND & 0xFC);
  
  return data;
}

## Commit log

2012-12-14 Initial commit, lots to do. - TX seems to be working okay - Backlight PWM is working okay - Ring buffer and RX stuff is in place but untested - IO code for the t6963 driver is in place but not tested
2012-12-15 Ring buffer works
2012-12-31 Renamed ks0107 files to ks0108 (that's the *real* chip involved) Add a meta-file for LCD functions.
    Right now, the ks0108 files don't work. I don't know why, but I'm
    about to radically alter them, so I wanted to freeze at this point
    so I can go back if I need to.
2012-12-31 Finally got writing to the ks0108b working. Let's commit here, so we have a failsafe, then I'm going to clean it up and start adding control over the second page of the display...
2012-12-31 Draw pixel implemented.
2013-01-07 Abstracted draw pixel to lcd.c
2013-01-07 Added a new line to the end of each file. Restructured includes to eliminate some warnings. Added lcdDrawLine() but haven't tested it yet. Moved configuration of LCD from main file to a config funtio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
2013-01-07 Add lcdConfig() to main
2013-01-07 Added an io_support file for IO configuration and read/write to the 8-bit non-concomitant data lines. ks0108bReadData doesn't work; trying to sort out why. Added putDec and putLine to serial. Added a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
2013-04-17 Minor changes, mostly debugging. - Moved LATrigger() to io_support - changes to glcdbp.c for debugging - Changes to ks0108b.c: - add lots of comments - change timing constants - add readblock functio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
2013-04-17 Finished work on line and pixel drawing - ks0108bReadData() needed some work - added a putBin() serial function to print binary output
2013-04-17 Added lcdDrawCircle(). It works!
2013-04-17 lcdDrawBox() is up and working.
2013-04-17 Added character display mode - added draw column to ks0108b and lcd - added draw character to lcd - added "cursor" tracking function to lcd - fixed character map array so characters display right sid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
2013-04-18 Begin work on serial UI - Added ui.c and ui.h - Implemented a pop function for serial buffer in serial.c - Add serial ring buffer access to serial.c - Adjust includes on lcd.h and lcd.c - begin to im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
    Command parsing not yet implemented; drawPixel doesn't work yet.
2013-04-19 Implement serial draw pixel and line
    - glcdbp.c: clear buffer after command receipt
    - lcd.c: add draw/erase pixel logic to all draw funcs
    - serial.c: fix ring buffer pop logic for end of buffer wrap
    - ui.c: add/fix draw line and pixel commands
2013-04-19 Added serial draw circle function
2013-04-19 Adding NVM stuff for settings
2013-04-19 Adding UI features
    - glcdbp.c: added 1 sec baud rate check delay
    rearrange init to support this
    added eeprom fetch for BL level and baud rate
    - io_support.h: commented some (probably) superfluous defines
    - serial.c: added a ring buffer clear function
    - ui.c: added a baud rate adjust function
2013-04-19 Implemented splash screen
    - glcdbp.c: added lcdDrawLogo() during startup
    - lcd.c: added lcdDrawLogo() function
    - lcd.h: added matrix for logo layout
2013-04-19 Add support for suppressing splash
2013-04-19 Added erase block function
2013-04-19 Added block erase to ui
2013-04-19 Enabled reverse mode
2013-04-21 Working on backspace, newline support Works on 0,0 origin, at least. - glcdbp.c: * changed the ring buffer depth to a settable constant, set to 256 * added logic to detect a new line or backspace key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
2013-04-21 Smashing a few warnings
2013-04-21 Make dimensions variable in lcd.c.
2013-04-22 Add command escape character
    - glcdbp.c: add '|' as an escape character to command mode
    - ks0108b.c: fixing some tab/space issues
    - lcd.c: added lcdDrawSprite(), but no functionality yet
    - lcd.h: same
2013-04-22 Added display size logic - glcdbp.c: * add lots of comments * add check for display size setting pin (PB3) - io_support.c: * add DISPLAY_TYPE enum * add display size check and large screen init code 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
2013-04-24 Sprite handling stuff
    - glcdbp.c: enable pull-ups during display check
    - io_support: remove LATrigger() function
    - ks0108b: altered readBlock() function to read an 8x8 block of pixels
    - lcd:
    * add drawSprite() function
    * add getBlock() function
2013-05-02 Large display integration nearly complete. glcdbp.c: - added delay to display discovery section - moved lcdConfig() farther down the execution order - added some whitespace and comments for readabili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
2013-05-02 Large screen should be done. glcdbp.c: comments only interrupt.c: comments only ks0108b.c: - remove unused ks0108bBusyWait() function - remove unused ks0108bDisplayOff() function - remove unused ks01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
2013-05-03 Clean up and comments - glcdbp.c: comments only - glcdbp.h: change buffer depth to 32, comments - interrupts.c: comments only - io_support.c: comments only - io_support.h: comments only - ks0108b.c: 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
2013-05-03 Added draw sprite to UI - glcdbp.c: uncomment 1s delay - t6963.c: remove debugging prints from readBlock - ui.c: * draw circle had a bug re: number of characters in command * added draw sprite method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
2013-05-03 Final cleanup- fixing some bugs, add demo. Chiefly, masking issues for sprites and the infamous 'd' changes the screen brightness on the small display. - Makefile: add demo.c - glcdbp.c: remove boot 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
2013-05-06 Add demo.c and demo.h
2013-07-02 Initial Hardware file commit
2013-07-08 Update label placements
2013-07-24 Fixed enable line issues for small LCD
2013-09-24 Fixed bug with long lines on lg disp
2013-09-26 Change serial input buffer depth to 256
2013-10-29 Adding Arduino Library
2013-11-13 Changed all ints to Bytes
    Cleaned up c files to be more efficient. Added Comments galore.
2013-11-13 Changed ints to Bytes - full
2013-11-13 uncommented some functions
2015-04-24 Initial commit.
2015-04-24 Removed .gitignore
2015-04-24 Moved AVR firmware to top-level Firmware folder.
2015-04-24 Squashed 'Libraries/Arduino/' content from commit 1deb108
    git-subtree-dir: Libraries/Arduino
    git-subtree-split: 1deb1086befaeaecd1500e15612a955c8936a6f0
2015-04-24 Rearraged for new Arduino library format.
2015-04-27 Moving example into proper structure, updating file names, updating library.properties
2015-04-27 Removing duplicate copies of AVR files in Arduino library
2015-12-31 created panel v16
2025-06-27 Update README.md
    Updating link

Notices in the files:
parts and their libraries:
SparkFun-Aesthetics: Licensing: CC v3.0 Share-Alike You are welcome to use this library for commercial purposes.
SparkFun-Retired: Licensing:Creative Commons ShareAlike 4.0 International - https://creativecommons.org/licenses/by-sa/4.0
